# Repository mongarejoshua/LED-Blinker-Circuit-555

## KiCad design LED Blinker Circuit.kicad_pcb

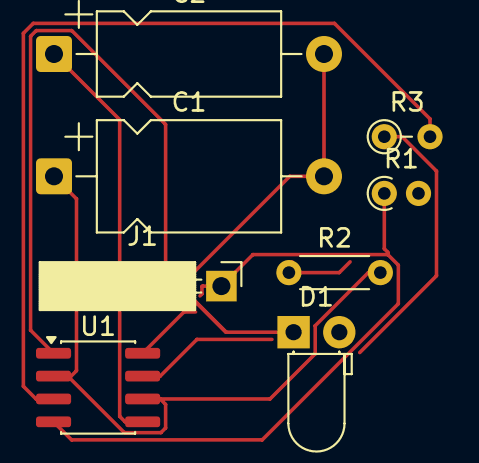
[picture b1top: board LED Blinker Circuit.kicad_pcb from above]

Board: 2 copper layers, 8 parts (0 on the bottom side), 7 nets.

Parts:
C1: 10u; CP_Axial_L10.0mm_D6.0mm_P15.00mm_Horizontal
C2: 10n; CP_Axial_L10.0mm_D4.5mm_P15.00mm_Horizontal
D1: LED; LED_D3.0mm_Horizontal_O1.27mm_Z2.0mm_Clear
J1: Conn_01x02_Pin; PinSocket_1x01_P2.54mm_Horizontal
R1: 1k; R_Axial_DIN0204_L3.6mm_D1.6mm_P1.90mm_Vertical
R2: 68k; R_Axial_DIN0204_L3.6mm_D1.6mm_P5.08mm_Horizontal
R3: 470; R_Axial_DIN0204_L3.6mm_D1.6mm_P2.54mm_Vertical
U1: NE555D; SOIC-8_3.9x4.9mm_P1.27mm

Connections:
+9V: J1.1, R1.1, U1.4 (R), U1.8 (VCC)
GND: C1.2, C2.2, D1.1 (K), U1.1 (GND)
unnamed: D1.2 (A), R3.1
unnamed: C2.1, U1.5 (CV)
unnamed: R1.2, R2.1, U1.7 (DIS)
unnamed: R3.2, U1.3 (Q)
unnamed: C1.1, R2.2, U1.2 (TR), U1.6 (THR)

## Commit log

2025-11-11 schematic update
2025-11-11 breadboard version
2025-11-13 Add screenshot to README
2025-11-13 screenshot update
2025-11-20 Update README with project tools
    Added tools used for the project in the README.
2025-11-20 visual demo update
2025-11-20 Replace local screenshot with external image links
    Updated images in the README to use external links.
